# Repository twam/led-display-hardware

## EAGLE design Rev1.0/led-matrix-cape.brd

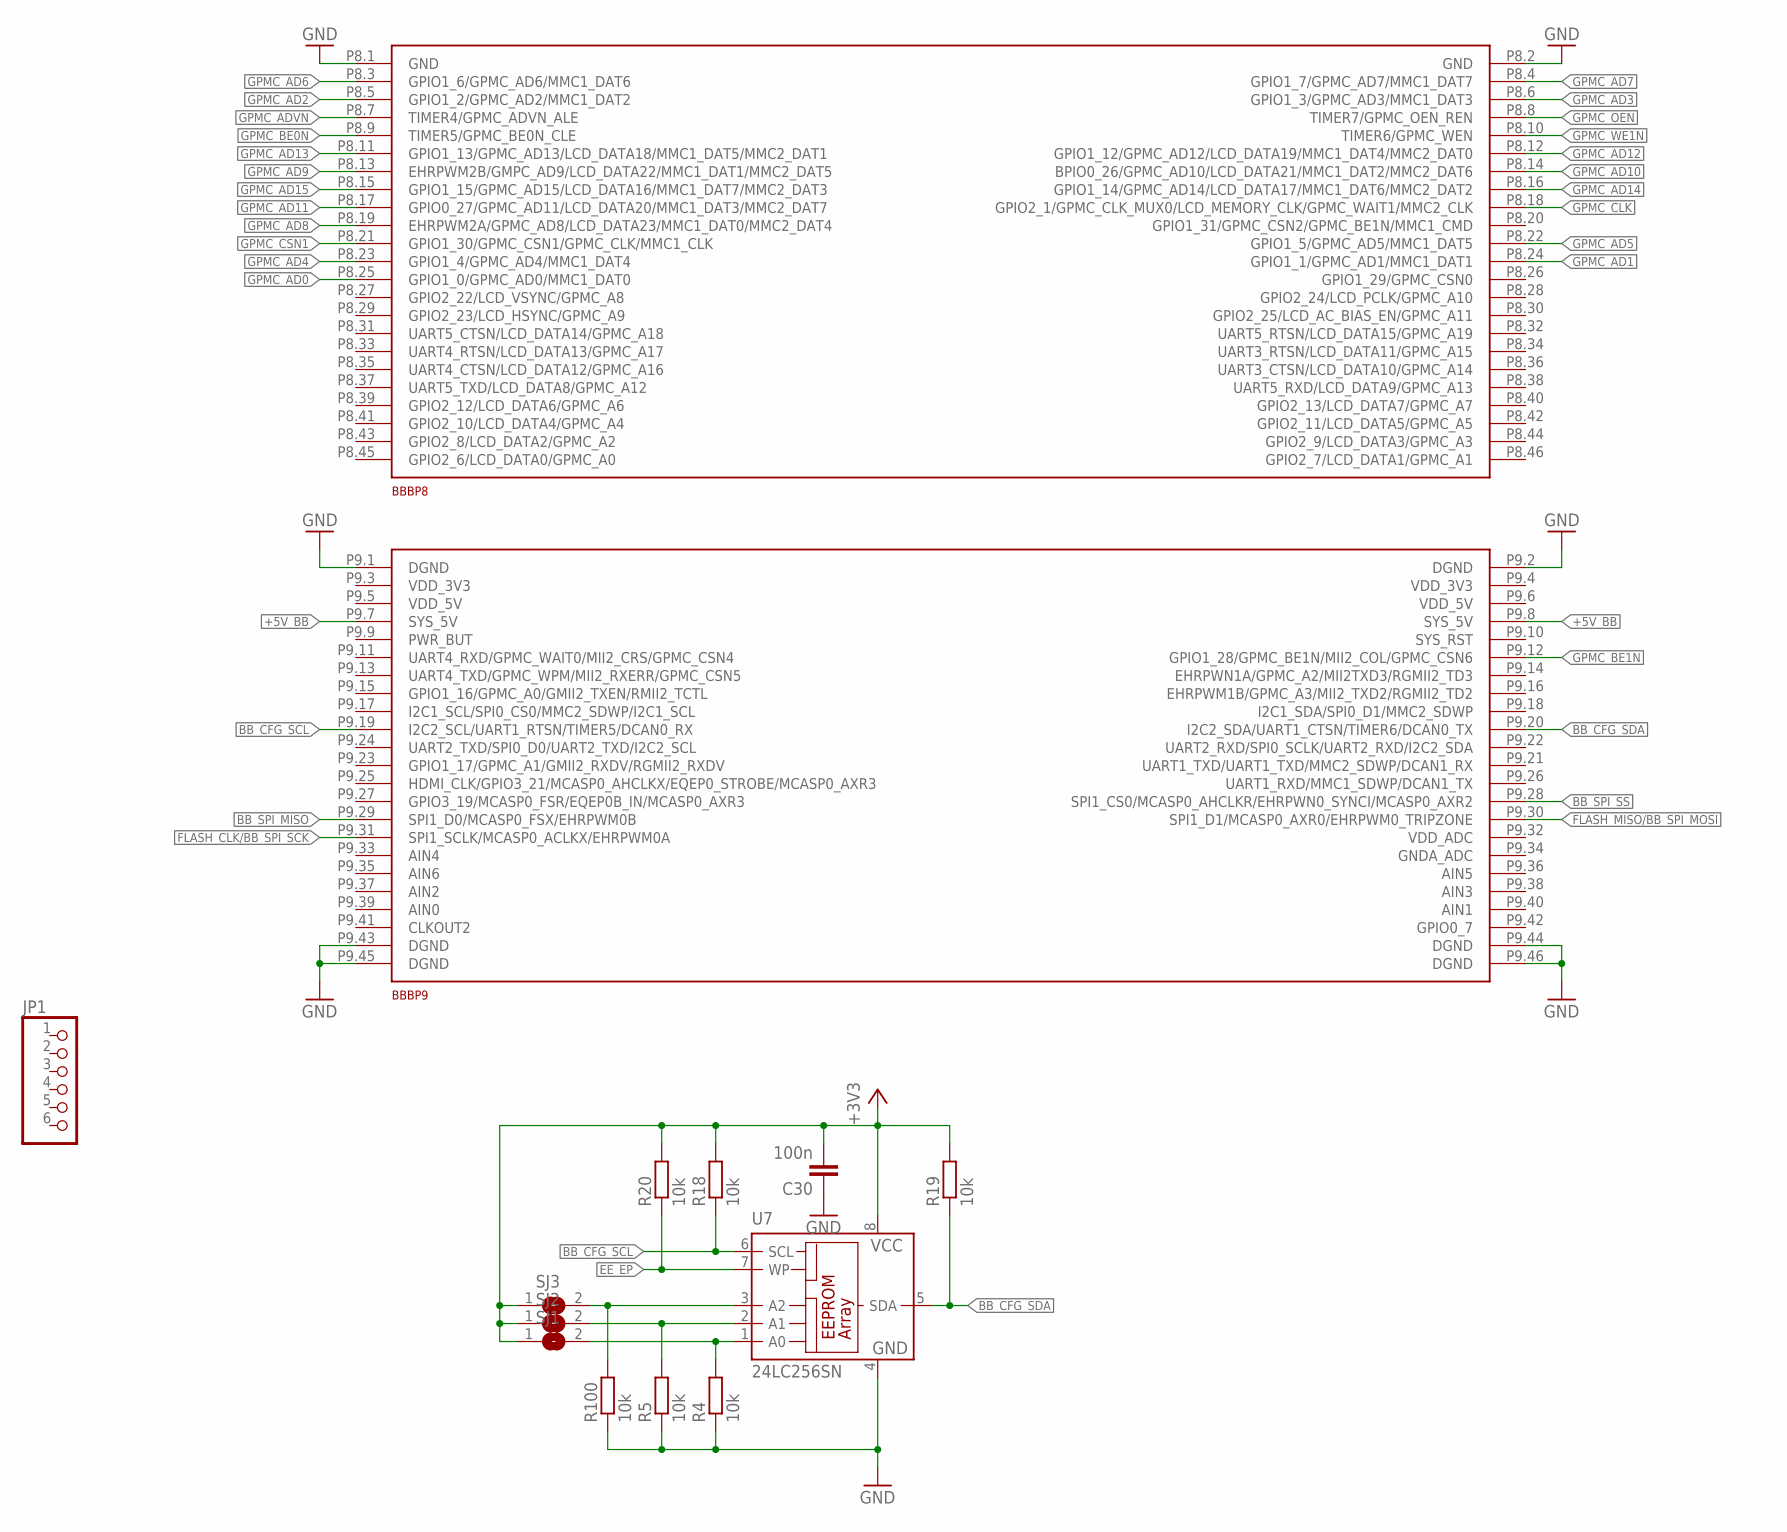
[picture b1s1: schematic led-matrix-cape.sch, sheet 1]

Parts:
BBB: BEAGLEBONE_CAPE_CONNECTORS; BEAGLEBONE_CAPE
C30: 100n; C0603
JP1: PINHD-1X6; 1X06
R4, R5, R18, R19, R20, R100: 10k; R0603
SJ1, SJ2, SJ3: SJ
U7: 24LC256SN; SO-08

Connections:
+3V3: C30.2, R18.2, R19.2, R20.2, SJ1.1, SJ2.1, SJ3.1, U7.8 (VCC); also elsewhere on the board
+5V_BB: BBB.P9.7 (SYS_5V), BBB.P9.8 (SYS_5V); also elsewhere on the board
ADDR0: R4.2, SJ1.2, U7.1 (A0)
ADDR1: R5.2, SJ2.2, U7.2 (A1)
ADDR2: R100.2, SJ3.2, U7.3 (A2)
BB_CFG_SCL: BBB.P9.19 (I2C2_SCL/UART1_RTSN/TIMER5/DCAN0_RX), R18.1, U7.6 (SCL); also elsewhere on the board
BB_CFG_SDA: BBB.P9.20 (I2C2_SDA/UART1_CTSN/TIMER6/DCAN0_TX), R19.1, U7.5 (SDA); also elsewhere on the board
BB_SPI_MISO: BBB.P9.29 (SPI1_D0/MCASP0_FSX/EHRPWM0B); also elsewhere on the board
BB_SPI_SS: BBB.P9.28 (SPI1_CS0/MCASP0_AHCLKR/EHRPWN0_SYNCI/MC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); also elsewhere on the board
EE_EP: R20.1, U7.7 (WP)
FLASH_CLK/BB_SPI_SCK: BBB.P9.31 (SPI1_SCLK/MCASP0_ACLKX/EHRPWM0A); also elsewhere on the board
FLASH_MISO/BB_SPI_MOSI: BBB.P9.30 (SPI1_D1/MCASP0_AXR0/EHRPWM0_TRIPZONE); also elsewhere on the board
GND: BBB.P8.1 (GND), BBB.P8.2 (GND), BBB.P9.1 (DGND), BBB.P9.2 (DGND), BBB.P9.43 (DGND), BBB.P9.44 (DGND), BBB.P9.45 (DGND), BBB.P9.46 (DGND), C30.1, R4.1, R5.1, R100.1, U7.4 (GND); also elsewhere on the board
GPMC_AD0: BBB.P8.25 (GPIO1_0/GPMC_AD0/MMC1_DAT0); also elsewhere on the board
GPMC_AD1: BBB.P8.24 (GPIO1_1/GPMC_AD1/MMC1_DAT1); also elsewhere on the board
GPMC_AD2: BBB.P8.5 (GPIO1_2/GPMC_AD2/MMC1_DAT2); also elsewhere on the board
GPMC_AD3: BBB.P8.6 (GPIO1_3/GPMC_AD3/MMC1_DAT3); also elsewhere on the board
GPMC_AD4: BBB.P8.23 (GPIO1_4/GPMC_AD4/MMC1_DAT4); also elsewhere on the board
GPMC_AD5: BBB.P8.22 (GPIO1_5/GPMC_AD5/MMC1_DAT5); also elsewhere on the board
GPMC_AD6: BBB.P8.3 (GPIO1_6/GPMC_AD6/MMC1_DAT6); also elsewhere on the board
GPMC_AD7: BBB.P8.4 (GPIO1_7/GPMC_AD7/MMC1_DAT7); also elsewhere on the board
GPMC_AD8: BBB.P8.19 (EHRPWM2A/GPMC_AD8/LCD_DATA23/MMC1_DAT0/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); also elsewhere on the board
GPMC_AD9: BBB.P8.13 (EHRPWM2B/GMPC_AD9/LCD_DATA22/MMC1_DAT1/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); also elsewhere on the board
GPMC_AD10: BBB.P8.14 (BPIO0_26/GPMC_AD10/LCD_DATA21/MMC1_DAT2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); also elsewhere on the board
GPMC_AD11: BBB.P8.17 (GPIO0_27/GPMC_AD11/LCD_DATA20/MMC1_DAT3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); also elsewhere on the board
GPMC_AD12: BBB.P8.12 (GPIO1_12/GPMC_AD12/LCD_DATA19/MMC1_DAT4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); also elsewhere on the board
GPMC_AD13: BBB.P8.11 (GPIO1_13/GPMC_AD13/LCD_DATA18/MMC1_DAT5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); also elsewhere on the board
GPMC_AD14: BBB.P8.16 (GPIO1_14/GPMC_AD14/LCD_DATA17/MMC1_DAT6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); also elsewhere on the board
GPMC_AD15: BBB.P8.15 (GPIO1_15/GPMC_AD15/LCD_DATA16/MMC1_DAT7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); also elsewhere on the board
GPMC_ADVN: BBB.P8.7 (TIMER4/GPMC_ADVN_ALE); also elsewhere on the board
GPMC_BE0N: BBB.P8.9 (TIMER5/GPMC_BE0N_CLE); also elsewhere on the board
GPMC_BE1N: BBB.P9.12 (GPIO1_28/GPMC_BE1N/MII2_COL/GPMC_CSN6); also elsewhere on the board
GPMC_CLK: BBB.P8.18 (GPIO2_1/GPMC_CLK_MUX0/LCD_MEMORY_CLK/GP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); also elsewhere on the board
GPMC_CSN1: BBB.P8.21 (GPIO1_30/GPMC_CSN1/GPMC_CLK/MMC1_CLK); also elsewhere on the board
GPMC_OEN: BBB.P8.8 (TIMER7/GPMC_OEN_REN); also elsewhere on the board
GPMC_WE1N: BBB.P8.10 (TIMER6/GPMC_WEN); also elsewhere on the board

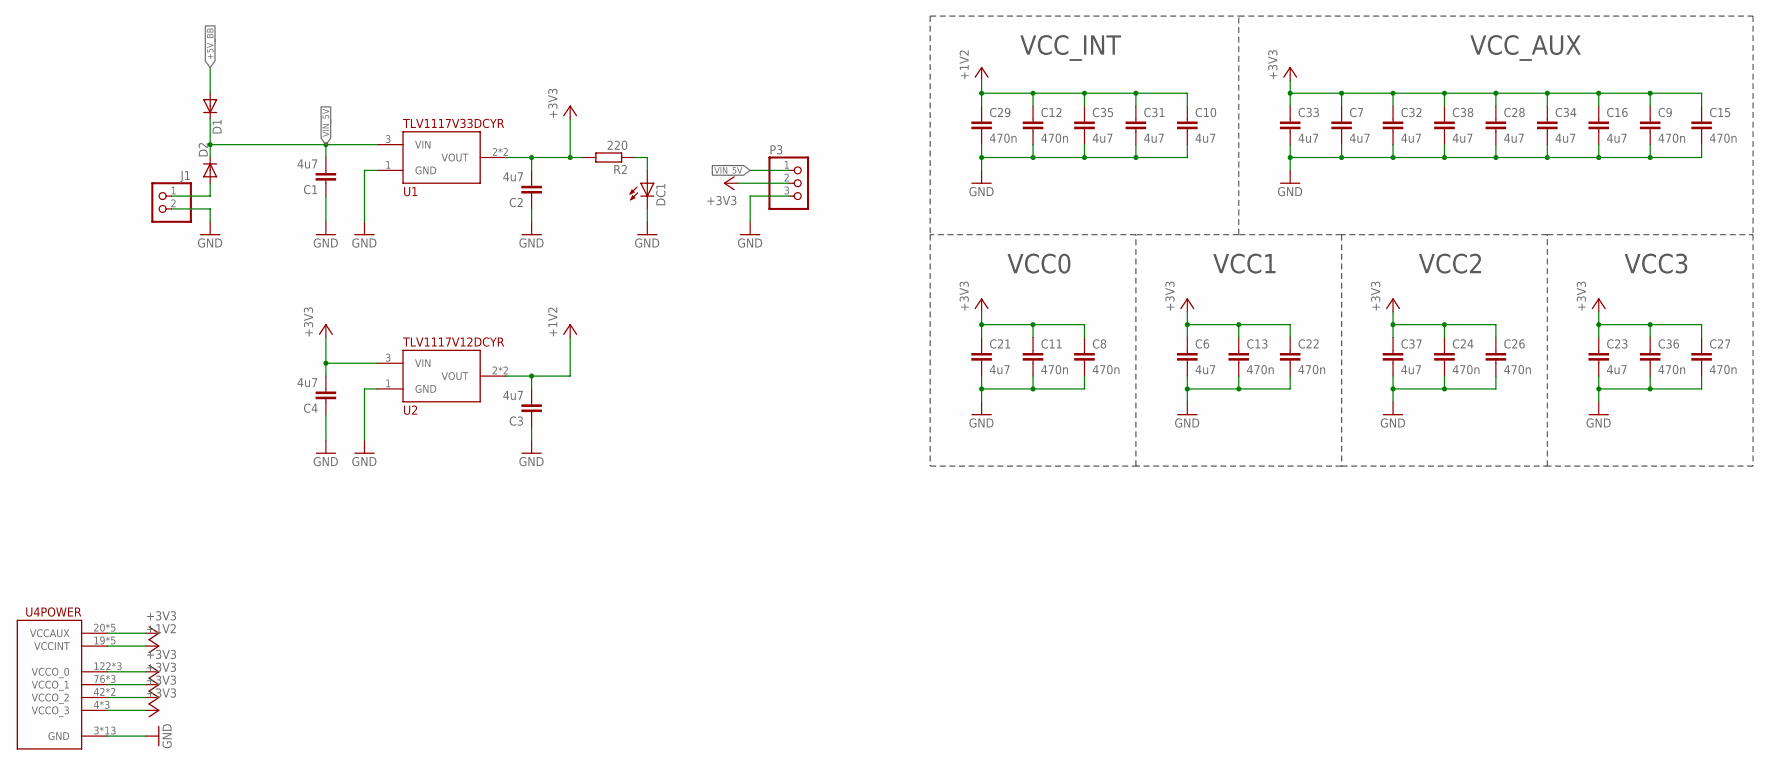
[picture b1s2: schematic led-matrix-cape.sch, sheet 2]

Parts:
C1, C2, C3, C4, C6, C7, C10, C16, C21, C23, C28, C31, C32, C33, C34, C35, C37, C38: 4u7; C0603
C8, C9, C11, C12, C13, C15, C22, C24, C26, C27, C29, C36: 470n; C0603
D1, D2: DIODE-SOD123; SOD123
DC1: LEDCHIP-LED0805; CHIP-LED0805
J1: PINHD-1X2; 1X02
P3: PINHD-1X3; 1X03
R2: 220; R0805
U1: TLV1117V33DCYR; SOT223
U2: TLV1117V12DCYR; SOT223
U4: XC6SLX9-2TQG144C; TQFP144

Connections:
+1V2: C3.2, C10.1, C12.1, C29.1, C31.1, C35.1, U2.2 (VOUT), U2.4 (VOUT), U4.19 (VCCINT), U4.28 (VCCINT), U4.52 (VCCINT), U4.89 (VCCINT), U4.128 (VCCINT)
+3V3: C2.2, C4.2, C6.1, C7.1, C8.1, C9.1, C11.1, C13.1, C15.1, C16.1, C21.1, C22.1, C23.1, C24.1, C26.1, C27.1, C28.1, C32.1, C33.1, C34.1, C36.1, C37.1, C38.1, P3.2, R2.2, U1.2 (VOUT), U1.4 (VOUT), U2.3 (VIN), U4.4 (VCCO_3), U4.18 (VCCO_3), U4.20 (VCCAUX), U4.31 (VCCO_3), U4.36 (VCCAUX), U4.42 (VCCO_2), U4.53 (VCCAUX), U4.63 (VCCO_2), U4.76 (VCCO_1), U4.86 (VCCO_1), U4.90 (VCCAUX), U4.103 (VCCO_1), U4.122 (VCCO_0), U4.125 (VCCO_0), U4.129 (VCCAUX), U4.135 (VCCO_0); also elsewhere on the board
+5V_BB: D1.A; also elsewhere on the board
GND: C1.1, C2.1, C3.1, C4.1, C6.2, C7.2, C8.2, C9.2, C10.2, C11.2, C12.2, C13.2, C15.2, C16.2, C21.2, C22.2, C23.2, C24.2, C26.2, C27.2, C28.2, C29.2, C31.2, C32.2, C33.2, C34.2, C35.2, C36.2, C37.2, C38.2, DC1.C, J1.2, P3.3, U1.1 (GND), U2.1 (GND), U4.3 (GND), U4.13 (GND), U4.25 (GND), U4.49 (GND), U4.54 (GND), U4.68 (GND), U4.77 (GND), U4.91 (GND), U4.96 (GND), U4.108 (GND), U4.113 (GND), U4.130 (GND), U4.136 (GND); also elsewhere on the board
unnamed: D2.A, J1.1
unnamed: DC1.A, R2.1
VIN_5V: C1.2, D1.C, D2.C, P3.1, U1.3 (VIN)

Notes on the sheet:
VCC_INT
VCC_AUX
VCC0
VCC1
VCC2
VCC3

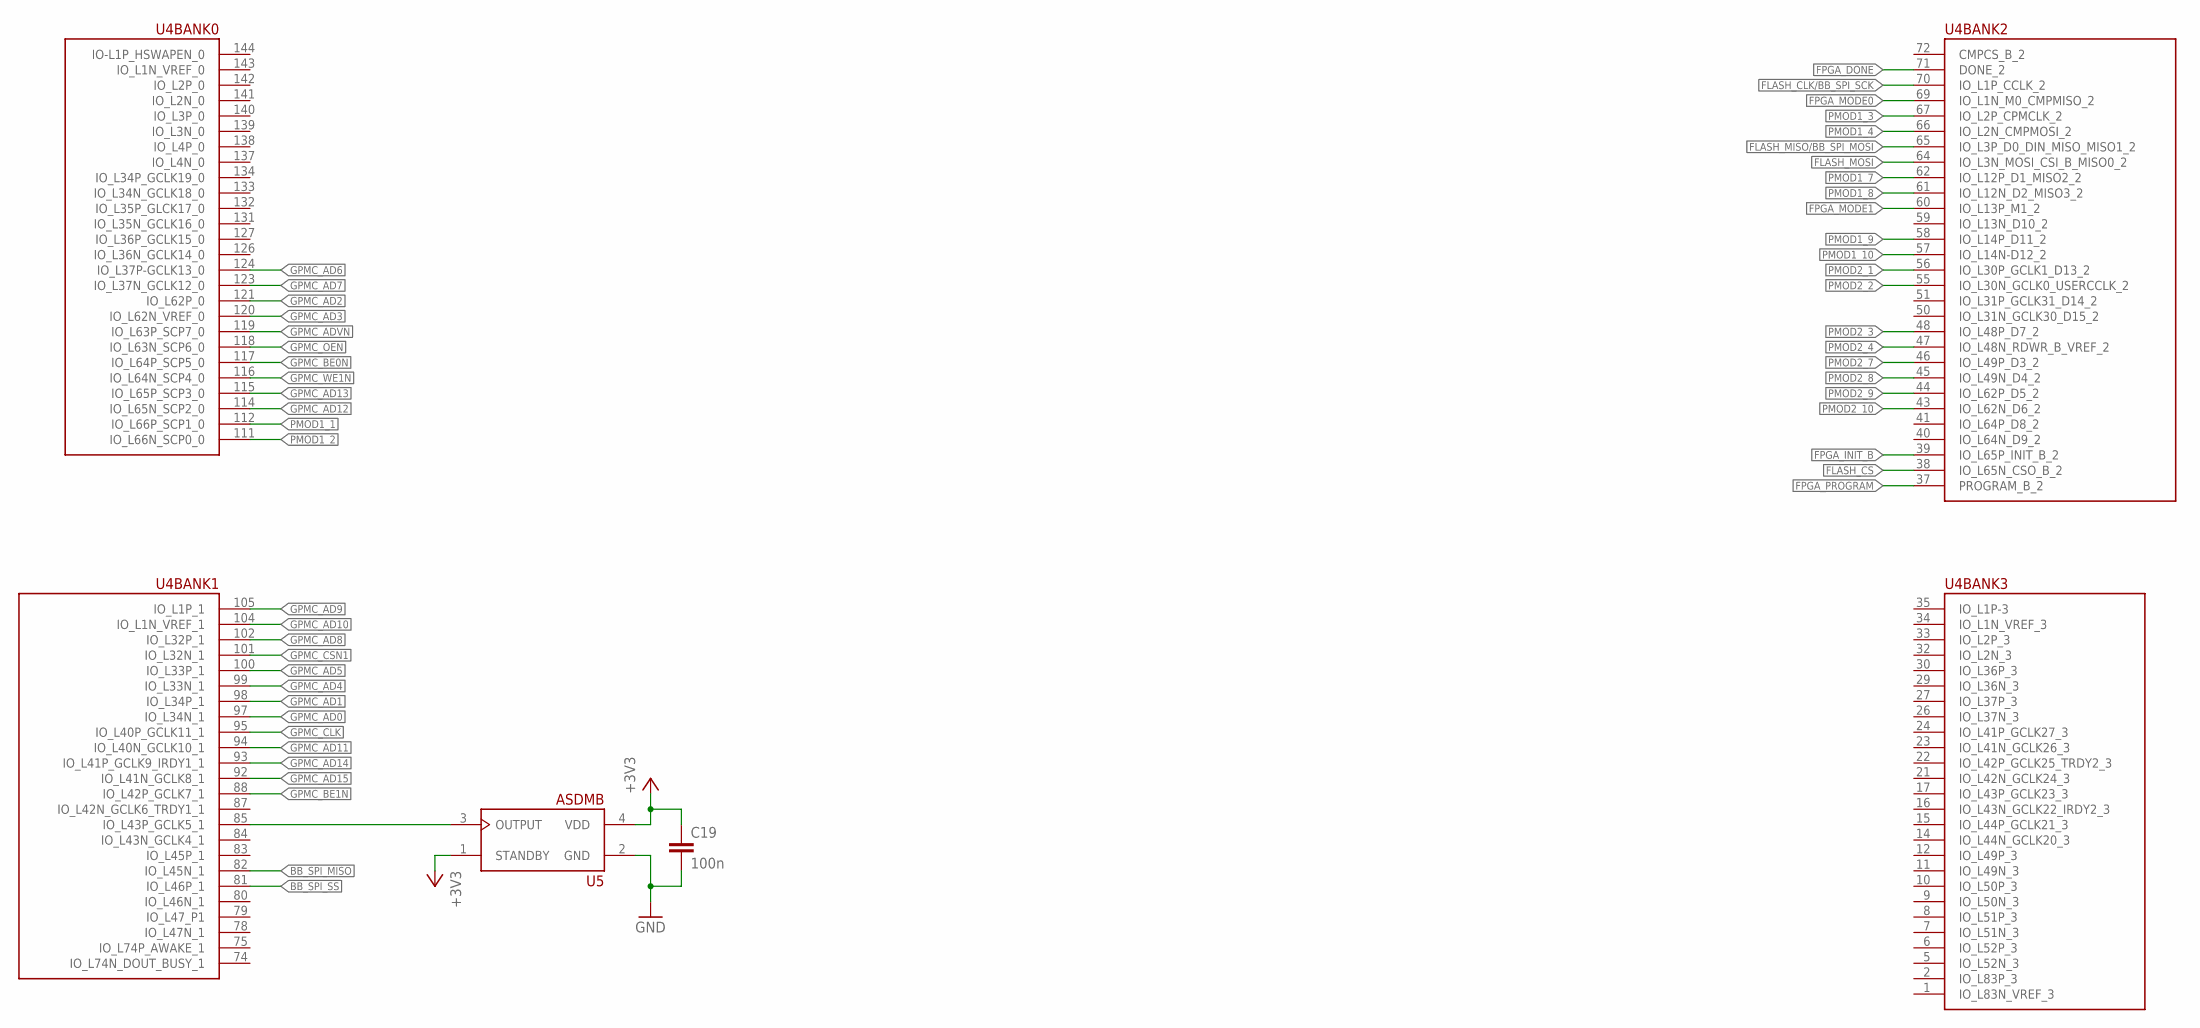
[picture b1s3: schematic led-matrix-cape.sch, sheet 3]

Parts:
C19: 100n; C0603
U4: XC6SLX9-2TQG144C; TQFP144
U5: ASDMB

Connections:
+3V3: C19.1, U5.1 (STANDBY), U5.4 (VDD); also elsewhere on the board
BB_SPI_MISO: U4.82 (IO_L45N_1); also elsewhere on the board
BB_SPI_SS: U4.81 (IO_L46P_1); also elsewhere on the board
FLASH_CLK/BB_SPI_SCK: U4.70 (IO_L1P_CCLK_2); also elsewhere on the board
FLASH_CS: U4.38 (IO_L65N_CSO_B_2); also elsewhere on the board
FLASH_MISO/BB_SPI_MOSI: U4.65 (IO_L3P_D0_DIN_MISO_MISO1_2); also elsewhere on the board
FLASH_MOSI: U4.64 (IO_L3N_MOSI_CSI_B_MISO0_2); also elsewhere on the board
FPGA_DONE: U4.71 (DONE_2); also elsewhere on the board
FPGA_INIT_B: U4.39 (IO_L65P_INIT_B_2); also elsewhere on the board
FPGA_MODE0: U4.69 (IO_L1N_M0_CMPMISO_2); also elsewhere on the board
FPGA_MODE1: U4.60 (IO_L13P_M1_2); also elsewhere on the board
FPGA_PROGRAM: U4.37 (PROGRAM_B_2); also elsewhere on the board
GND: C19.2, U5.2 (GND); also elsewhere on the board
GPMC_AD0: U4.97 (IO_L34N_1); also elsewhere on the board
GPMC_AD1: U4.98 (IO_L34P_1); also elsewhere on the board
GPMC_AD2: U4.121 (IO_L62P_0); also elsewhere on the board
GPMC_AD3: U4.120 (IO_L62N_VREF_0); also elsewhere on the board
GPMC_AD4: U4.99 (IO_L33N_1); also elsewhere on the board
GPMC_AD5: U4.100 (IO_L33P_1); also elsewhere on the board
GPMC_AD6: U4.124 (IO_L37P-GCLK13_0); also elsewhere on the board
GPMC_AD7: U4.123 (IO_L37N_GCLK12_0); also elsewhere on the board
GPMC_AD8: U4.102 (IO_L32P_1); also elsewhere on the board
GPMC_AD9: U4.105 (IO_L1P_1); also elsewhere on the board
GPMC_AD10: U4.104 (IO_L1N_VREF_1); also elsewhere on the board
GPMC_AD11: U4.94 (IO_L40N_GCLK10_1); also elsewhere on the board
GPMC_AD12: U4.114 (IO_L65N_SCP2_0); also elsewhere on the board
GPMC_AD13: U4.115 (IO_L65P_SCP3_0); also elsewhere on the board
GPMC_AD14: U4.93 (IO_L41P_GCLK9_IRDY1_1); also elsewhere on the board
GPMC_AD15: U4.92 (IO_L41N_GCLK8_1); also elsewhere on the board
GPMC_ADVN: U4.119 (IO_L63P_SCP7_0); also elsewhere on the board
GPMC_BE0N: U4.117 (IO_L64P_SCP5_0); also elsewhere on the board
GPMC_BE1N: U4.88 (IO_L42P_GCLK7_1); also elsewhere on the board
GPMC_CLK: U4.95 (IO_L40P_GCLK11_1); also elsewhere on the board
GPMC_CSN1: U4.101 (IO_L32N_1); also elsewhere on the board
GPMC_OEN: U4.118 (IO_L63N_SCP6_0); also elsewhere on the board
GPMC_WE1N: U4.116 (IO_L64N_SCP4_0); also elsewhere on the board
OSC_FPGA: U4.85 (IO_L43P_GCLK5_1), U5.3 (OUTPUT)
PMOD1_1: U4.112 (IO_L66P_SCP1_0); also elsewhere on the board
PMOD1_2: U4.111 (IO_L66N_SCP0_0); also elsewhere on the board
PMOD1_3: U4.67 (IO_L2P_CPMCLK_2); also elsewhere on the board
PMOD1_4: U4.66 (IO_L2N_CMPMOSI_2); also elsewhere on the board
PMOD1_7: U4.62 (IO_L12P_D1_MISO2_2); also elsewhere on the board
PMOD1_8: U4.61 (IO_L12N_D2_MISO3_2); also elsewhere on the board
PMOD1_9: U4.58 (IO_L14P_D11_2); also elsewhere on the board
PMOD1_10: U4.57 (IO_L14N-D12_2); also elsewhere on the board
PMOD2_1: U4.56 (IO_L30P_GCLK1_D13_2); also elsewhere on the board
PMOD2_2: U4.55 (IO_L30N_GCLK0_USERCCLK_2); also elsewhere on the board
PMOD2_3: U4.48 (IO_L48P_D7_2); also elsewhere on the board
PMOD2_4: U4.47 (IO_L48N_RDWR_B_VREF_2); also elsewhere on the board
PMOD2_7: U4.46 (IO_L49P_D3_2); also elsewhere on the board
PMOD2_8: U4.45 (IO_L49N_D4_2); also elsewhere on the board
PMOD2_9: U4.44 (IO_L62P_D5_2); also elsewhere on the board
PMOD2_10: U4.43 (IO_L62N_D6_2); also elsewhere on the board

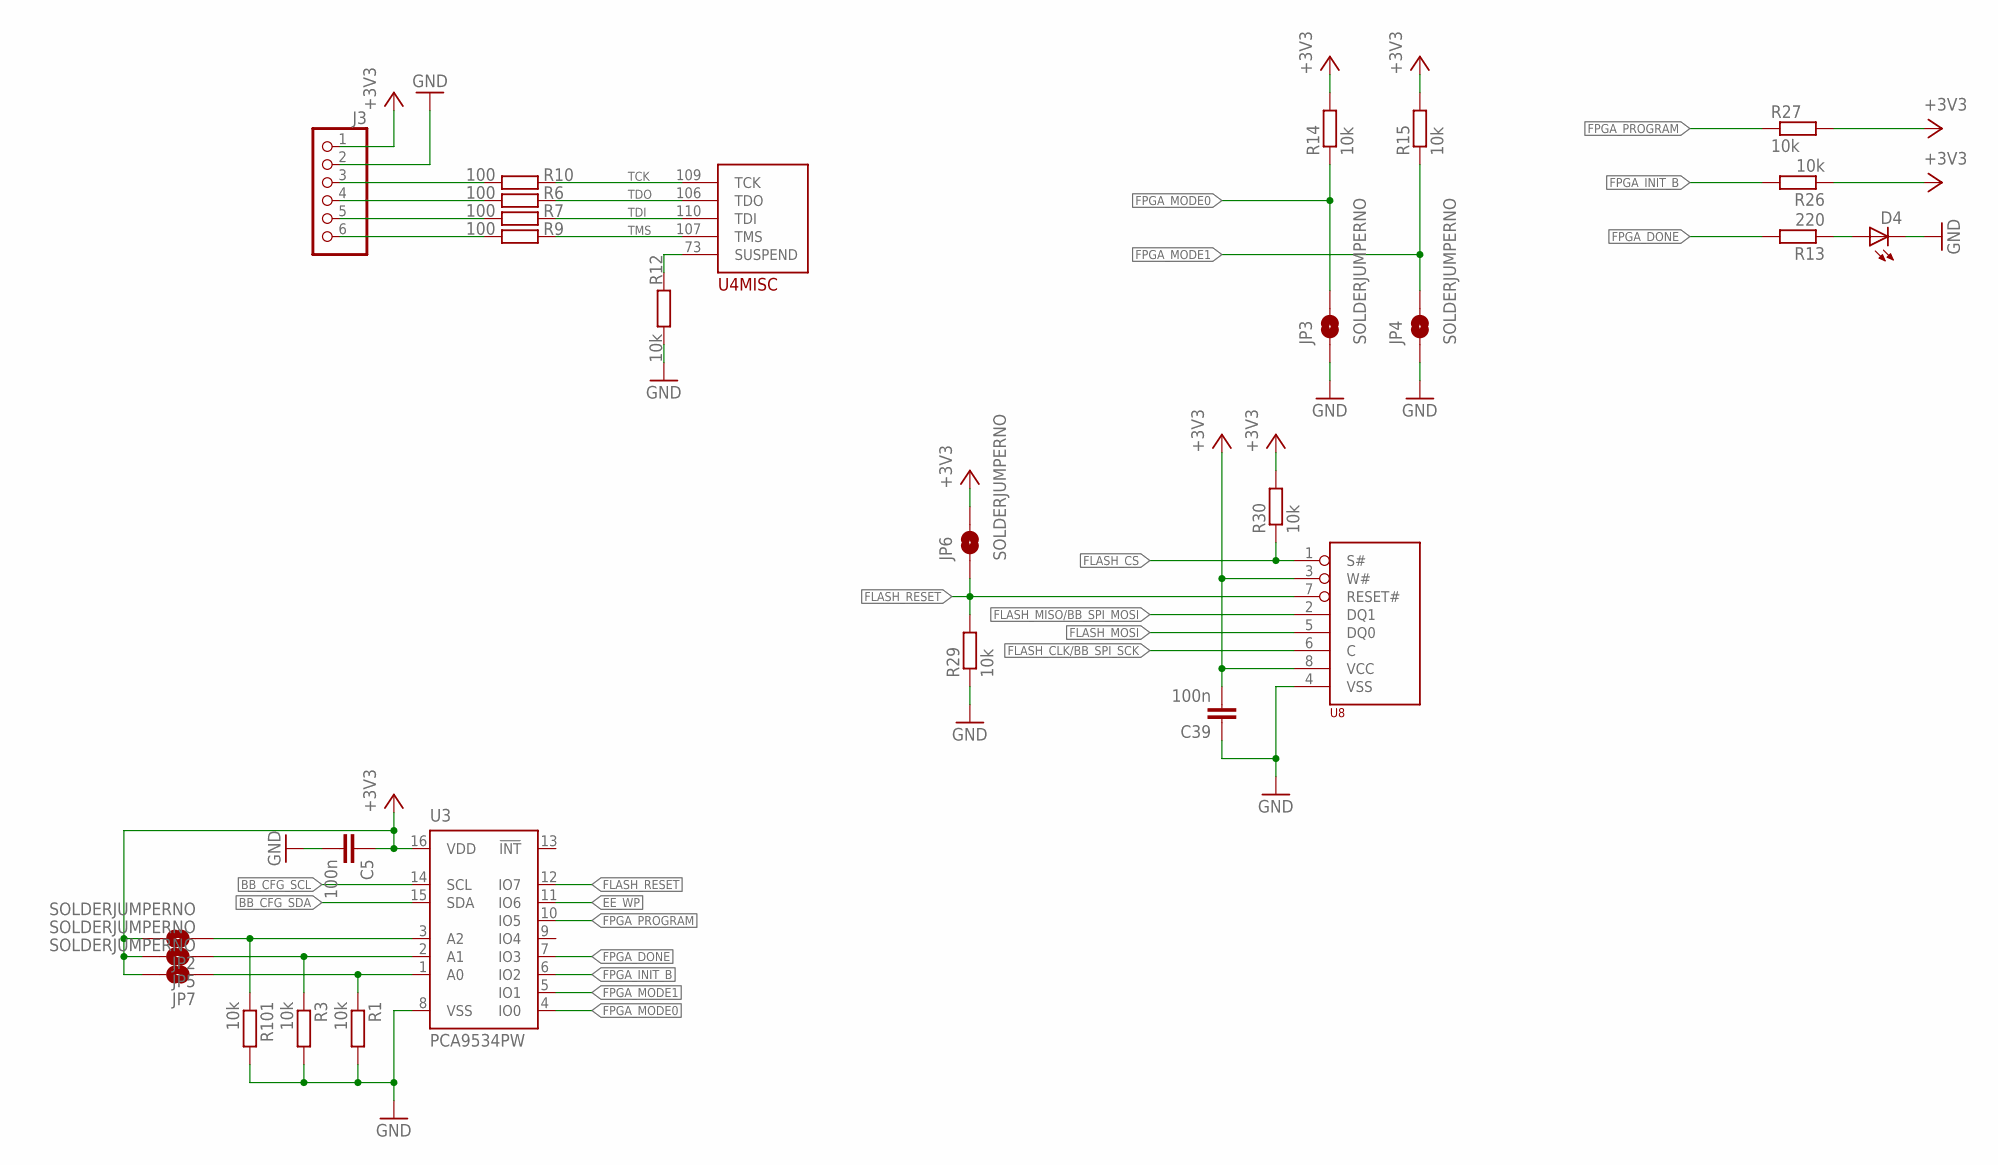
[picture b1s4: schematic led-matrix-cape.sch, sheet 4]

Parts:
C5, C39: 100n; C0603
D4: LEDCHIP-LED0805; CHIP-LED0805
J3: PINHD-1X6; 1X06
JP2, JP3, JP4, JP5, JP6, JP7: SOLDERJUMPERNO; SJ_2S-NO
R1, R3, R12, R14, R15, R26, R27, R30, R101: 10k; R0603
R6, R7, R9, R10: 100; R0603
R13: 220; R0603
R29: 10k; R0805
U3: PCA9534PW; TSSOP16
U4: XC6SLX9-2TQG144C; TQFP144
U8: M25PE16; SO8

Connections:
+3V3: C5.1, C39.2, J3.1, JP2.2, JP5.2, JP6.2, JP7.2, R14.2, R15.2, R26.1, R27.2, R30.2, U3.16 (VDD), U8.3 (W#), U8.8 (VCC); also elsewhere on the board
BB_CFG_SCL: U3.14 (SCL); also elsewhere on the board
BB_CFG_SDA: U3.15 (SDA); also elsewhere on the board
EE_WP: U3.11 (IO6)
FLASH_CLK/BB_SPI_SCK: U8.6 (C); also elsewhere on the board
FLASH_CS: R30.1, U8.1 (S#); also elsewhere on the board
FLASH_MISO/BB_SPI_MOSI: U8.2 (DQ1); also elsewhere on the board
FLASH_MOSI: U8.5 (DQ0); also elsewhere on the board
FLASH_RESET: JP6.1, R29.2, U3.12 (IO7), U8.7 (RESET#)
FPGA_DONE: R13.2, U3.7 (IO3); also elsewhere on the board
FPGA_INIT_B: R26.2, U3.6 (IO2); also elsewhere on the board
FPGA_MODE0: JP3.2, R14.1, U3.4 (IO0); also elsewhere on the board
FPGA_MODE1: JP4.2, R15.1, U3.5 (IO1); also elsewhere on the board
FPGA_PROGRAM: R27.1, U3.10 (IO5); also elsewhere on the board
GND: C5.2, C39.1, D4.C, J3.2, JP3.1, JP4.1, R1.2, R3.2, R12.1, R29.1, R101.2, U3.8 (VSS), U8.4 (VSS); also elsewhere on the board
unnamed: JP7.1, R1.1, U3.1 (A0)
unnamed: JP5.1, R3.1, U3.2 (A1)
unnamed: JP2.1, R101.1, U3.3 (A2)
unnamed: J3.3, R10.1
unnamed: J3.4, R6.1
unnamed: J3.5, R7.1
unnamed: J3.6, R9.1
unnamed: D4.A, R13.1
SUSPEND: R12.2, U4.73 (SUSPEND)
TCK: R10.2, U4.109 (TCK)
TDI: R7.2, U4.110 (TDI)
TDO: R6.2, U4.106 (TDO)
TMS: R9.2, U4.107 (TMS)

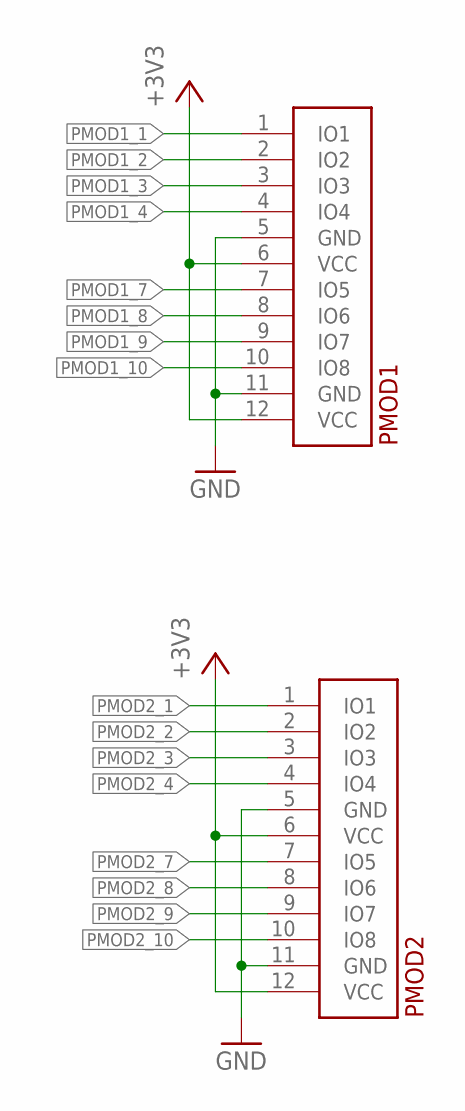
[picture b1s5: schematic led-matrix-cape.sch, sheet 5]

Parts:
PMOD1, PMOD2: PMOD_2_HOST

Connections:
+3V3: PMOD1.6 (VCC), PMOD1.12 (VCC), PMOD2.6 (VCC), PMOD2.12 (VCC); also elsewhere on the board
GND: PMOD1.5 (GND), PMOD1.11 (GND), PMOD2.5 (GND), PMOD2.11 (GND); also elsewhere on the board
PMOD1_1: PMOD1.1 (IO1); also elsewhere on the board
PMOD1_2: PMOD1.2 (IO2); also elsewhere on the board
PMOD1_3: PMOD1.3 (IO3); also elsewhere on the board
PMOD1_4: PMOD1.4 (IO4); also elsewhere on the board
PMOD1_7: PMOD1.7 (IO5); also elsewhere on the board
PMOD1_8: PMOD1.8 (IO6); also elsewhere on the board
PMOD1_9: PMOD1.9 (IO7); also elsewhere on the board
PMOD1_10: PMOD1.10 (IO8); also elsewhere on the board
PMOD2_1: PMOD2.1 (IO1); also elsewhere on the board
PMOD2_2: PMOD2.2 (IO2); also elsewhere on the board
PMOD2_3: PMOD2.3 (IO3); also elsewhere on the board
PMOD2_4: PMOD2.4 (IO4); also elsewhere on the board
PMOD2_7: PMOD2.7 (IO5); also elsewhere on the board
PMOD2_8: PMOD2.8 (IO6); also elsewhere on the board
PMOD2_9: PMOD2.9 (IO7); also elsewhere on the board
PMOD2_10: PMOD2.10 (IO8); also elsewhere on the board

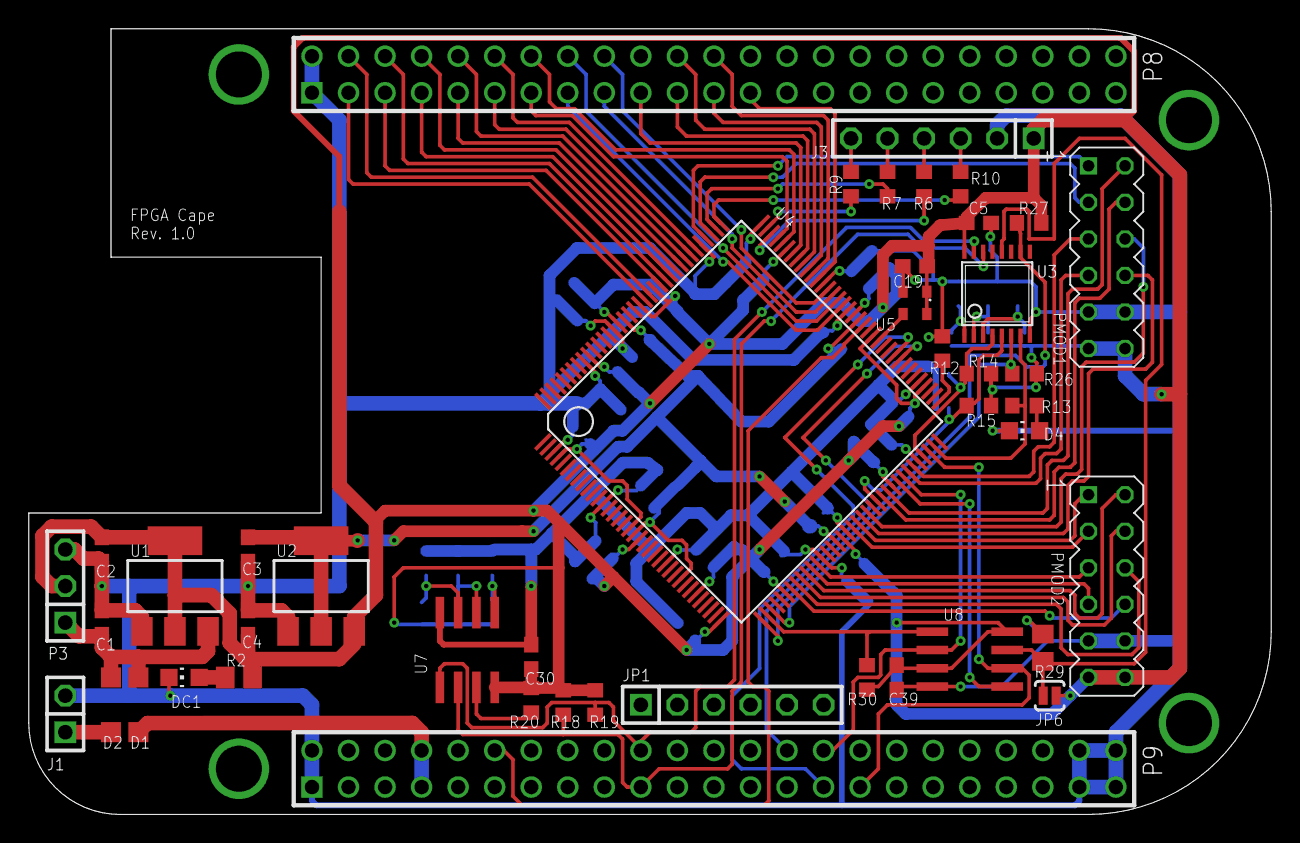
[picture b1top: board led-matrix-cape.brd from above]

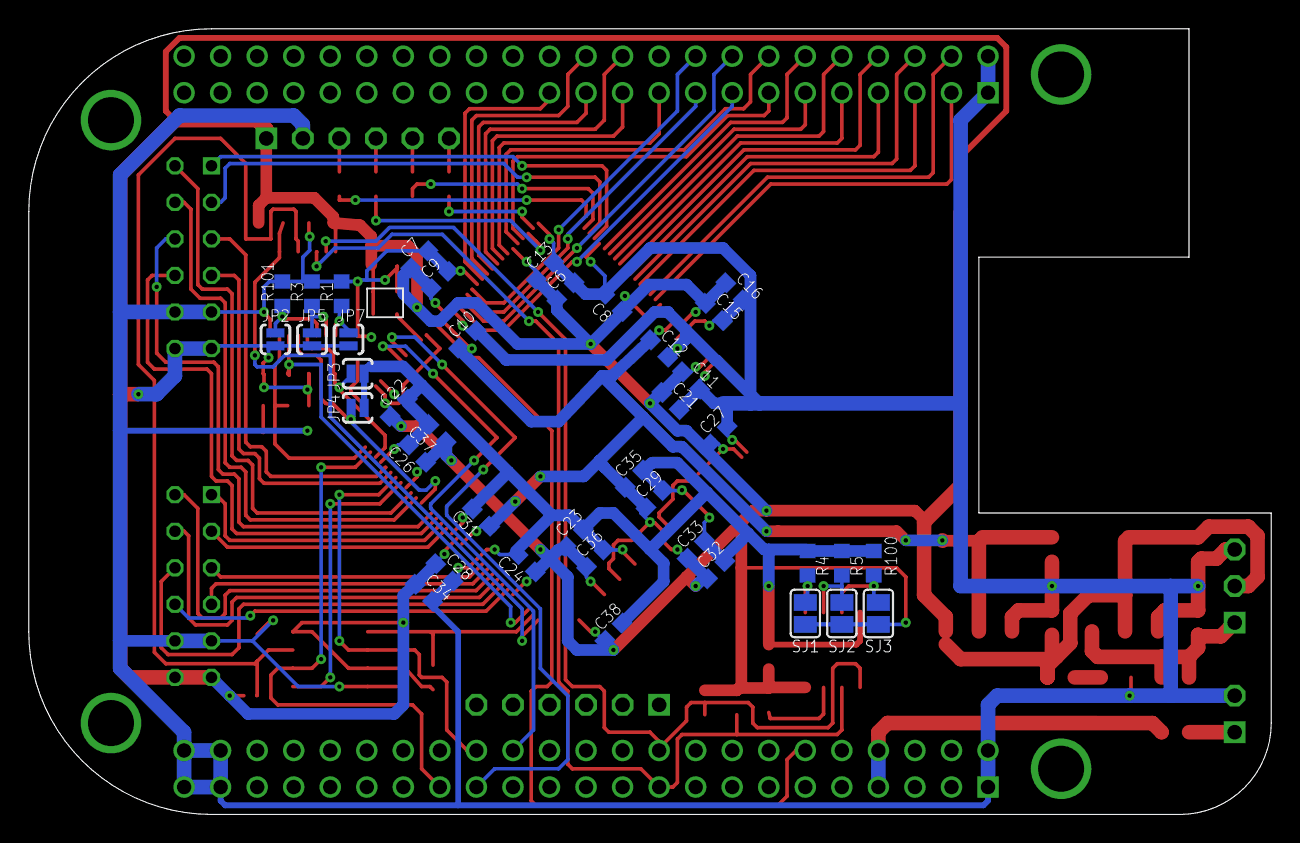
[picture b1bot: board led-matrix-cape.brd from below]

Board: 2 copper layers, 86.4 x 54.6 mm, 83 parts (40 on the bottom side), 78 nets.

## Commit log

2015-06-09 Rev 1.0 board
2015-06-09 Rev 2.0 board

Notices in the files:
parts and their libraries:
sparkfun: Licensing: CC v3.0 Share-Alike You are welcome to use this library for commercial purposes.
